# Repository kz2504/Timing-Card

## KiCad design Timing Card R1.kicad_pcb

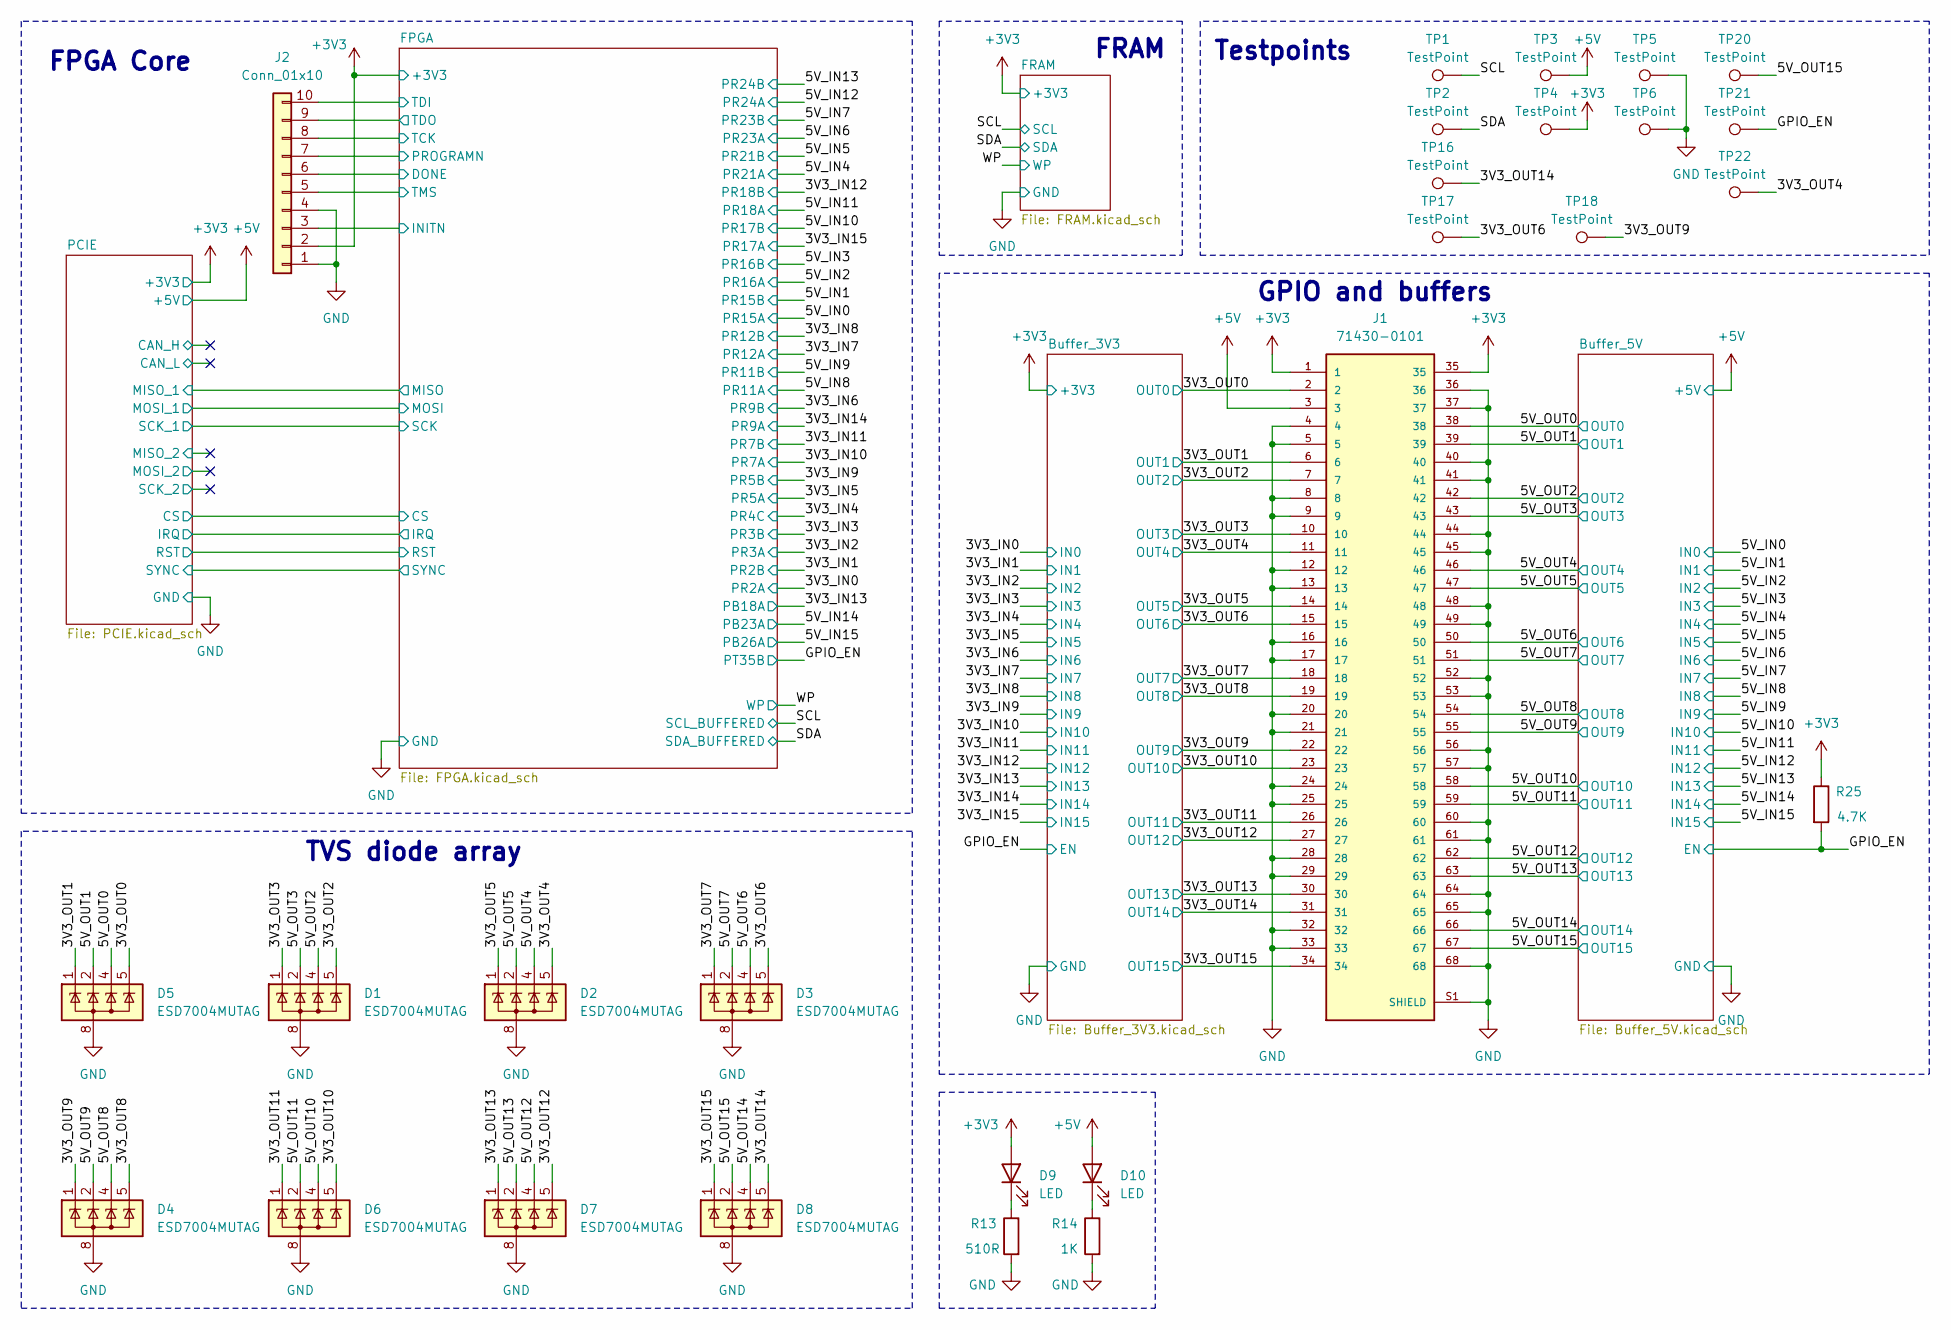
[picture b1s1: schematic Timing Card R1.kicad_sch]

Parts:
D1, D2, D3, D4, D5, D6, D7, D8: ESD7004MUTAG; Diodes_UDFN-10_1x2.5mm_P0.5mm_Modified
D9, D10: LED; LED_0805_2012Metric
J1: 71430-0101; MOLEX_71430-0101; PARTREV N
J2: Conn_01x10; PinHeader_2x05_P2.54mm_Vertical
R13: 510R; R_0805_2012Metric
R14: 1K; R_0805_2012Metric
R25: 4.7K; R_0805_2012Metric
TP1, TP2, TP3, TP4, TP5, TP6, TP16, TP17, TP18, TP20, TP21, TP22: TestPoint; TestPoint_Pad_D1.0mm

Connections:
+3V3: D9.2 (A), J1.1, J1.35, J2.2, R25.1, TP4.1; also elsewhere on the board
+5V: D10.2 (A), J1.3, TP3.1; also elsewhere on the board
/3V3_OUT0: D5.5 (K), J1.2; also elsewhere on the board
/3V3_OUT1: D5.1 (K), J1.6; also elsewhere on the board
/3V3_OUT2: D1.5 (K), J1.7; also elsewhere on the board
/3V3_OUT3: D1.1 (K), J1.10; also elsewhere on the board
/3V3_OUT4: D2.5 (K), J1.11, TP22.1; also elsewhere on the board
/3V3_OUT5: D2.1 (K), J1.14; also elsewhere on the board
/3V3_OUT6: D3.5 (K), J1.15, TP17.1; also elsewhere on the board
/3V3_OUT7: D3.1 (K), J1.18; also elsewhere on the board
/3V3_OUT8: D4.5 (K), J1.19; also elsewhere on the board
/3V3_OUT9: D4.1 (K), J1.22, TP18.1; also elsewhere on the board
/3V3_OUT10: D6.5 (K), J1.23; also elsewhere on the board
/3V3_OUT11: D6.1 (K), J1.26; also elsewhere on the board
/3V3_OUT12: D7.5 (K), J1.27; also elsewhere on the board
/3V3_OUT13: D7.1 (K), J1.30; also elsewhere on the board
/3V3_OUT14: D8.5 (K), J1.31, TP16.1; also elsewhere on the board
/3V3_OUT15: D8.1 (K), J1.34; also elsewhere on the board
/5V_OUT0: D5.4 (K), J1.38; also elsewhere on the board
/5V_OUT1: D5.2 (K), J1.39; also elsewhere on the board
/5V_OUT2: D1.4 (K), J1.42; also elsewhere on the board
/5V_OUT3: D1.2 (K), J1.43; also elsewhere on the board
/5V_OUT4: D2.4 (K), J1.46; also elsewhere on the board
/5V_OUT5: D2.2 (K), J1.47; also elsewhere on the board
/5V_OUT6: D3.4 (K), J1.50; also elsewhere on the board
/5V_OUT7: D3.2 (K), J1.51; also elsewhere on the board
/5V_OUT8: D4.4 (K), J1.54; also elsewhere on the board
/5V_OUT9: D4.2 (K), J1.55; also elsewhere on the board
/5V_OUT10: D6.4 (K), J1.58; also elsewhere on the board
/5V_OUT11: D6.2 (K), J1.59; also elsewhere on the board
/5V_OUT12: D7.4 (K), J1.62; also elsewhere on the board
/5V_OUT13: D7.2 (K), J1.63; also elsewhere on the board
/5V_OUT14: D8.4 (K), J1.66; also elsewhere on the board
/5V_OUT15: D8.2 (K), J1.67, TP20.1; also elsewhere on the board
/FPGA/DONE: J2.6; also elsewhere on the board
/FPGA/INITN: J2.3; also elsewhere on the board
/FPGA/PROGRAMN: J2.7; also elsewhere on the board
/FPGA/TCK: J2.8; also elsewhere on the board
/FPGA/TDI: J2.10; also elsewhere on the board
/FPGA/TDO: J2.9; also elsewhere on the board
/FPGA/TMS: J2.5; also elsewhere on the board
/GPIO_EN: R25.2, TP21.1; also elsewhere on the board
/SCL: TP1.1; also elsewhere on the board
/SDA: TP2.1; also elsewhere on the board
GND: D1.3 (A), D1.8 (A), D2.3 (A), D2.8 (A), D3.3 (A), D3.8 (A), D4.3 (A), D4.8 (A), D5.3 (A), D5.8 (A), D6.3 (A), D6.8 (A), D7.3 (A), D7.8 (A), D8.3 (A), D8.8 (A), J1.4, J1.5, J1.8, J1.9, J1.12, J1.13, J1.16, J1.17, J1.20, J1.21, J1.24, J1.25, J1.28, J1.29, J1.32, J1.33, J1.36, J1.37, J1.40, J1.41, J1.44, J1.45, J1.48, J1.49, J1.52, J1.53, J1.56, J1.57, J1.60, J1.61, J1.64, J1.65, J1.68, J1.S1 (SHIELD), J1.S2 (SHIELD), J2.1, J2.4, R13.2, R14.2, TP5.1, TP6.1; also elsewhere on the board
unnamed: D9.1 (K), R13.1
unnamed: D10.1 (K), R14.1

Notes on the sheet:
FRAM
FPGA Core
Testpoints
GPIO and buffers
TVS diode array

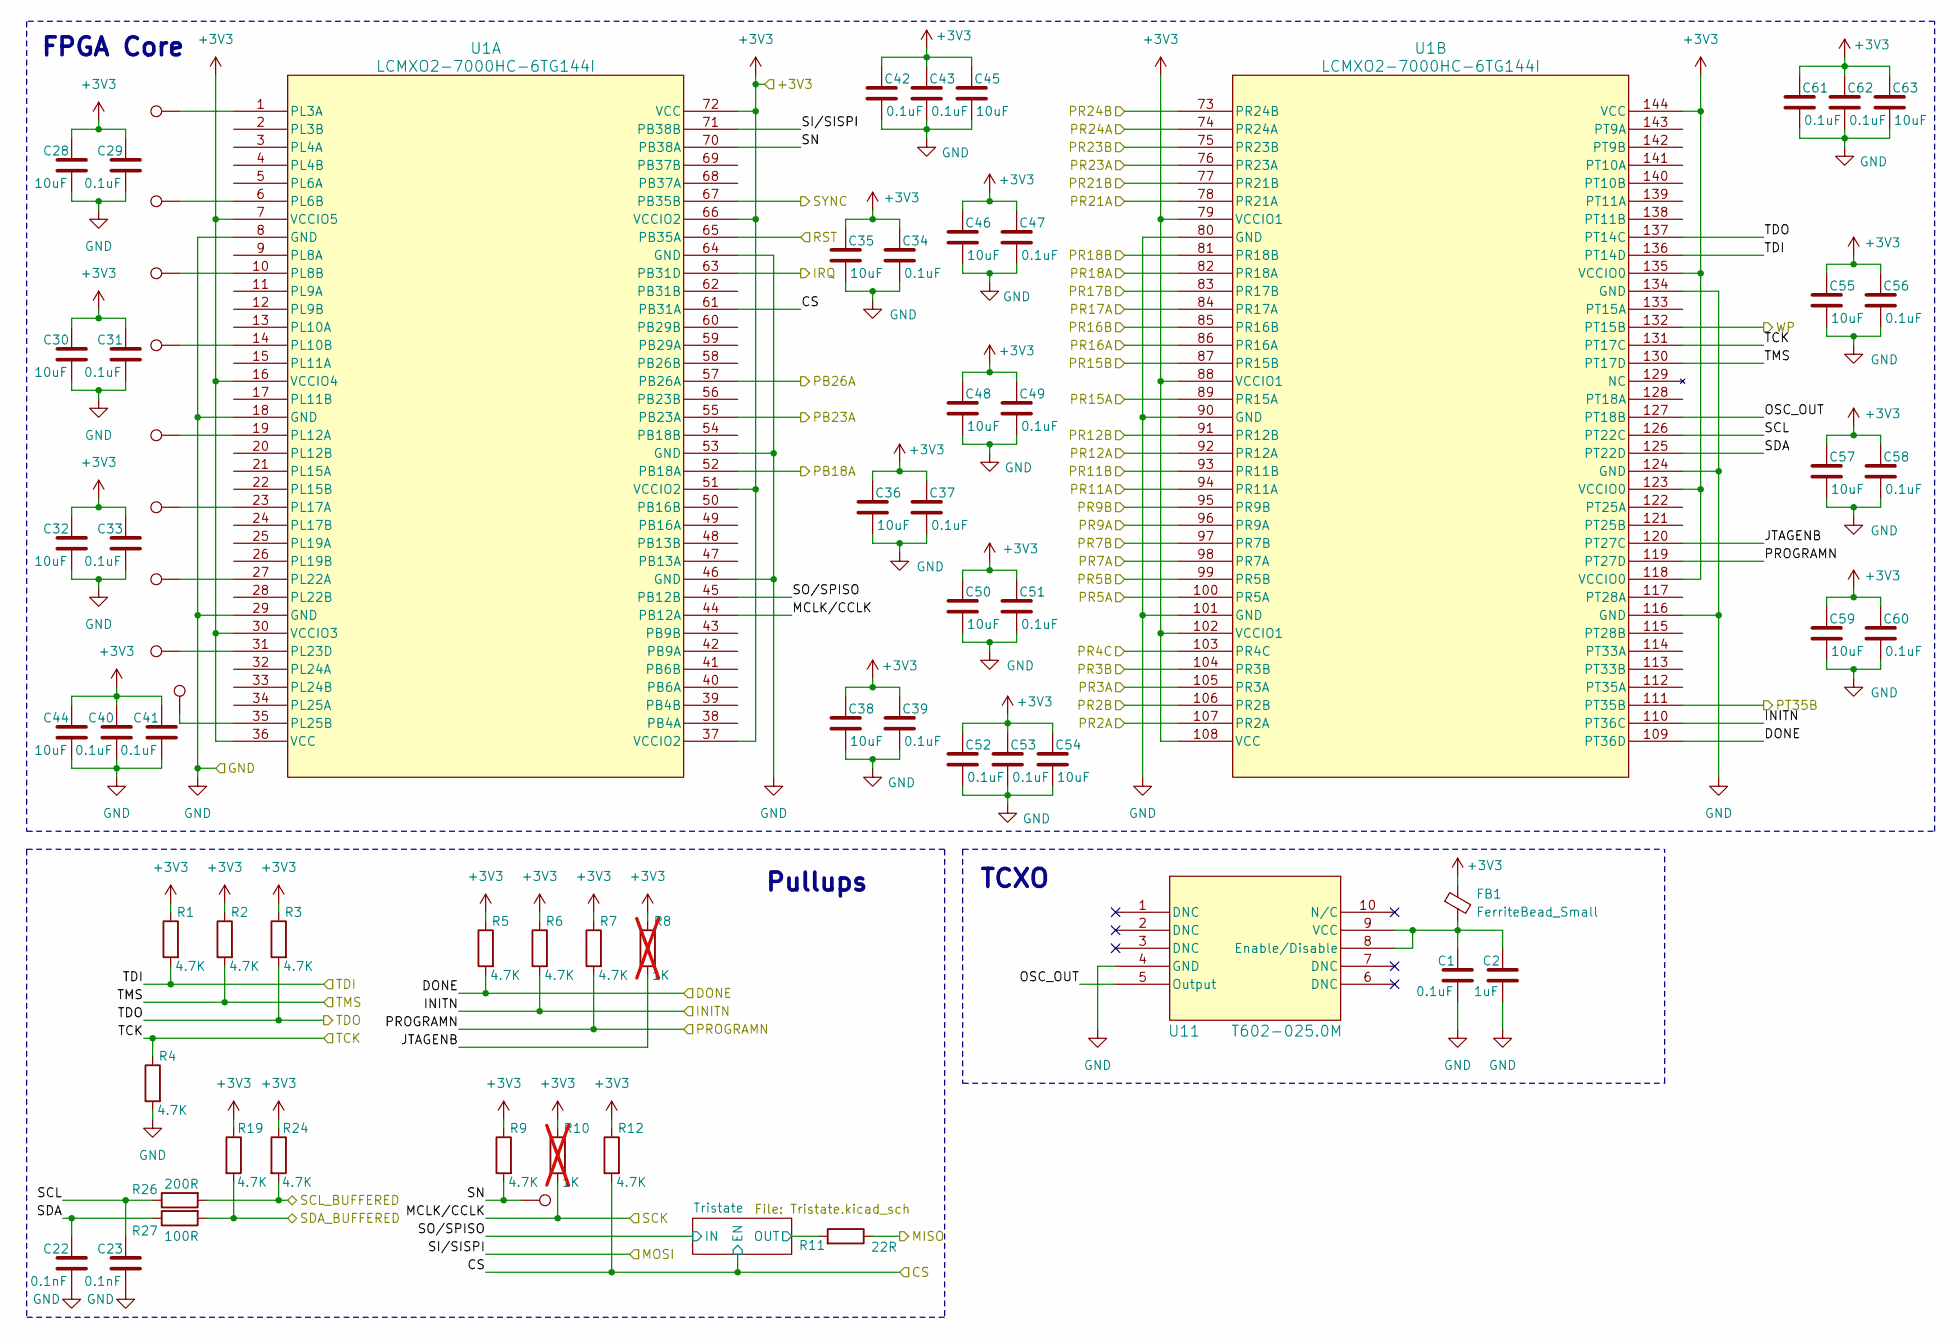
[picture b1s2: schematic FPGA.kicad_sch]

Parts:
C1: 0.1uF; C_0805_2012Metric
C2: 1uF; C_0805_2012Metric
C22, C23: 0.1nF; C_0805_2012Metric
C28, C30, C32, C35, C36, C38, C44, C45, C46, C48, C50, C54, C55, C57, C59, C63: 10uF; C_0603_1608Metric
C29, C31, C33, C34, C37, C39, C40, C41, C42, C43, C47, C49, C51, C52, C53, C56, C58, C60, C61, C62: 0.1uF; C_0603_1608Metric
FB1: FerriteBead_Small; L_0805_2012Metric
R1, R2, R3, R4, R5, R6, R7, R9, R12, R19, R24: 4.7K; R_0805_2012Metric
R8, R10: 1K; R_0805_2012Metric; not fitted
R11: 22R; R_0805_2012Metric
R26: 200R; R_0805_2012Metric
R27: 100R; R_0805_2012Metric
TP7, TP8, TP9, TP10, TP11, TP12, TP13, TP14, TP15: TestPoint; TestPoint_Pad_1.0x1.0mm
TP19: TestPoint; TestPoint_Pad_D1.0mm
U1: LCMXO2-7000HC-6TG144I; TQFP144_LAT
U11: T602-025.0M; T602-025.0M_CNW

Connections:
+3V3: C28.1, C29.1, C30.1, C31.1, C32.1, C33.1, C34.1, C35.1, C36.1, C37.1, C38.1, C39.1, C40.1, C41.1, C42.1, C43.1, C44.1, C45.1, C46.1, C47.1, C48.1, C49.1, C50.1, C51.1, C52.1, C53.1, C54.1, C55.1, C56.1, C57.1, C58.1, C59.1, C60.1, C61.1, C62.1, C63.1, FB1.1, R1.1, R2.1, R3.1, R5.1, R6.1, R7.1, R8.1, R9.1, R10.1, R12.1, R19.1, R24.1, U1.7 (VCCIO5), U1.16 (VCCIO4), U1.30 (VCCIO3), U1.36 (VCC), U1.37 (VCCIO2), U1.51 (VCCIO2), U1.66 (VCCIO2), U1.72 (VCC), U1.79 (VCCIO1), U1.88 (VCCIO1), U1.102 (VCCIO1), U1.108 (VCC), U1.118 (VCCIO0), U1.123 (VCCIO0), U1.135 (VCCIO0), U1.144 (VCC); also elsewhere on the board
/3V3_IN0: U1.107 (PR2A); also elsewhere on the board
/3V3_IN1: U1.106 (PR2B); also elsewhere on the board
/3V3_IN2: U1.105 (PR3A); also elsewhere on the board
/3V3_IN3: U1.104 (PR3B); also elsewhere on the board
/3V3_IN4: U1.103 (PR4C); also elsewhere on the board
/3V3_IN5: U1.100 (PR5A); also elsewhere on the board
/3V3_IN6: U1.95 (PR9B); also elsewhere on the board
/3V3_IN7: U1.92 (PR12A); also elsewhere on the board
/3V3_IN8: U1.91 (PR12B); also elsewhere on the board
/3V3_IN9: U1.99 (PR5B); also elsewhere on the board
/3V3_IN10: U1.98 (PR7A); also elsewhere on the board
/3V3_IN11: U1.97 (PR7B); also elsewhere on the board
/3V3_IN12: U1.81 (PR18B); also elsewhere on the board
/3V3_IN13: U1.52 (PB18A); also elsewhere on the board
/3V3_IN14: U1.96 (PR9A); also elsewhere on the board
/3V3_IN15: U1.84 (PR17A); also elsewhere on the board
/5V_IN0: U1.89 (PR15A); also elsewhere on the board
/5V_IN1: U1.87 (PR15B); also elsewhere on the board
/5V_IN2: U1.86 (PR16A); also elsewhere on the board
/5V_IN3: U1.85 (PR16B); also elsewhere on the board
/5V_IN4: U1.78 (PR21A); also elsewhere on the board
/5V_IN5: U1.77 (PR21B); also elsewhere on the board
/5V_IN6: U1.76 (PR23A); also elsewhere on the board
/5V_IN7: U1.75 (PR23B); also elsewhere on the board
/5V_IN8: U1.94 (PR11A); also elsewhere on the board
/5V_IN9: U1.93 (PR11B); also elsewhere on the board
/5V_IN10: U1.83 (PR17B); also elsewhere on the board
/5V_IN11: U1.82 (PR18A); also elsewhere on the board
/5V_IN12: U1.74 (PR24A); also elsewhere on the board
/5V_IN13: U1.73 (PR24B); also elsewhere on the board
/5V_IN14: U1.55 (PB23A); also elsewhere on the board
/5V_IN15: U1.57 (PB26A); also elsewhere on the board
/FPGA/CS: R12.2, U1.61 (PB31A); also elsewhere on the board
/FPGA/DONE: R5.2, U1.109 (PT36D); also elsewhere on the board
/FPGA/INITN: R6.2, U1.110 (PT36C); also elsewhere on the board
/FPGA/IRQ: U1.63 (PB31D); also elsewhere on the board
/FPGA/JTAGENB: R8.2, U1.120 (PT27C)
/FPGA/MCLK/CCLK: R10.2, U1.44 (PB12A); also elsewhere on the board
/FPGA/MISO: R11.1; also elsewhere on the board
/FPGA/OSC_OUT: U1.127 (PT18B), U11.5 (Output)
/FPGA/PROGRAMN: R7.2, U1.119 (PT27D); also elsewhere on the board
/FPGA/RST: U1.65 (PB35A); also elsewhere on the board
/FPGA/SCL: C23.1, R26.1, U1.126 (PT22C)
/FPGA/SDA: C22.1, R27.1, U1.125 (PT22D)
/FPGA/SI/SISPI: U1.71 (PB38B); also elsewhere on the board
/FPGA/SN: R9.2, TP19.1, U1.70 (PB38A)
/FPGA/SO/SPISO: U1.45 (PB12B); also elsewhere on the board
/FPGA/SYNC: U1.67 (PB35B); also elsewhere on the board
/FPGA/TCK: R4.1, U1.131 (PT17C); also elsewhere on the board
/FPGA/TDI: R1.2, U1.136 (PT14D); also elsewhere on the board
/FPGA/TDO: R3.2, U1.137 (PT14C); also elsewhere on the board
/FPGA/TMS: R2.2, U1.130 (PT17D); also elsewhere on the board
/FPGA/Tristate/OUT: R11.2; also elsewhere on the board
/GPIO_EN: U1.111 (PT35B); also elsewhere on the board
/SCL: R24.2, R26.2; also elsewhere on the board
/SDA: R19.2, R27.2; also elsewhere on the board
/WP: U1.132 (PT15B); also elsewhere on the board
GND: C1.2, C2.2, C22.2, C23.2, C28.2, C29.2, C30.2, C31.2, C32.2, C33.2, C34.2, C35.2, C36.2, C37.2, C38.2, C39.2, C40.2, C41.2, C42.2, C43.2, C44.2, C45.2, C46.2, C47.2, C48.2, C49.2, C50.2, C51.2, C52.2, C53.2, C54.2, C55.2, C56.2, C57.2, C58.2, C59.2, C60.2, C61.2, C62.2, C63.2, R4.2, U1.8 (GND), U1.18 (GND), U1.29 (GND), U1.46 (GND), U1.53 (GND), U1.64 (GND), U1.80 (GND), U1.90 (GND), U1.101 (GND), U1.116 (GND), U1.124 (GND), U1.134 (GND), U11.4 (GND); also elsewhere on the board
unnamed: TP7.1, U1.1 (PL3A)
unnamed: TP8.1, U1.6 (PL6B)
unnamed: TP9.1, U1.10 (PL8B)
unnamed: TP10.1, U1.14 (PL10B)
unnamed: TP11.1, U1.19 (PL12A)
unnamed: TP12.1, U1.23 (PL17A)
unnamed: TP13.1, U1.27 (PL22A)
unnamed: TP14.1, U1.31 (PL23D)
unnamed: TP15.1, U1.35 (PL25B)
unnamed: C1.1, C2.1, FB1.2, U11.8 (Enable/Disable), U11.9 (VCC)

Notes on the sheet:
TCXO
Pullups
FPGA Core

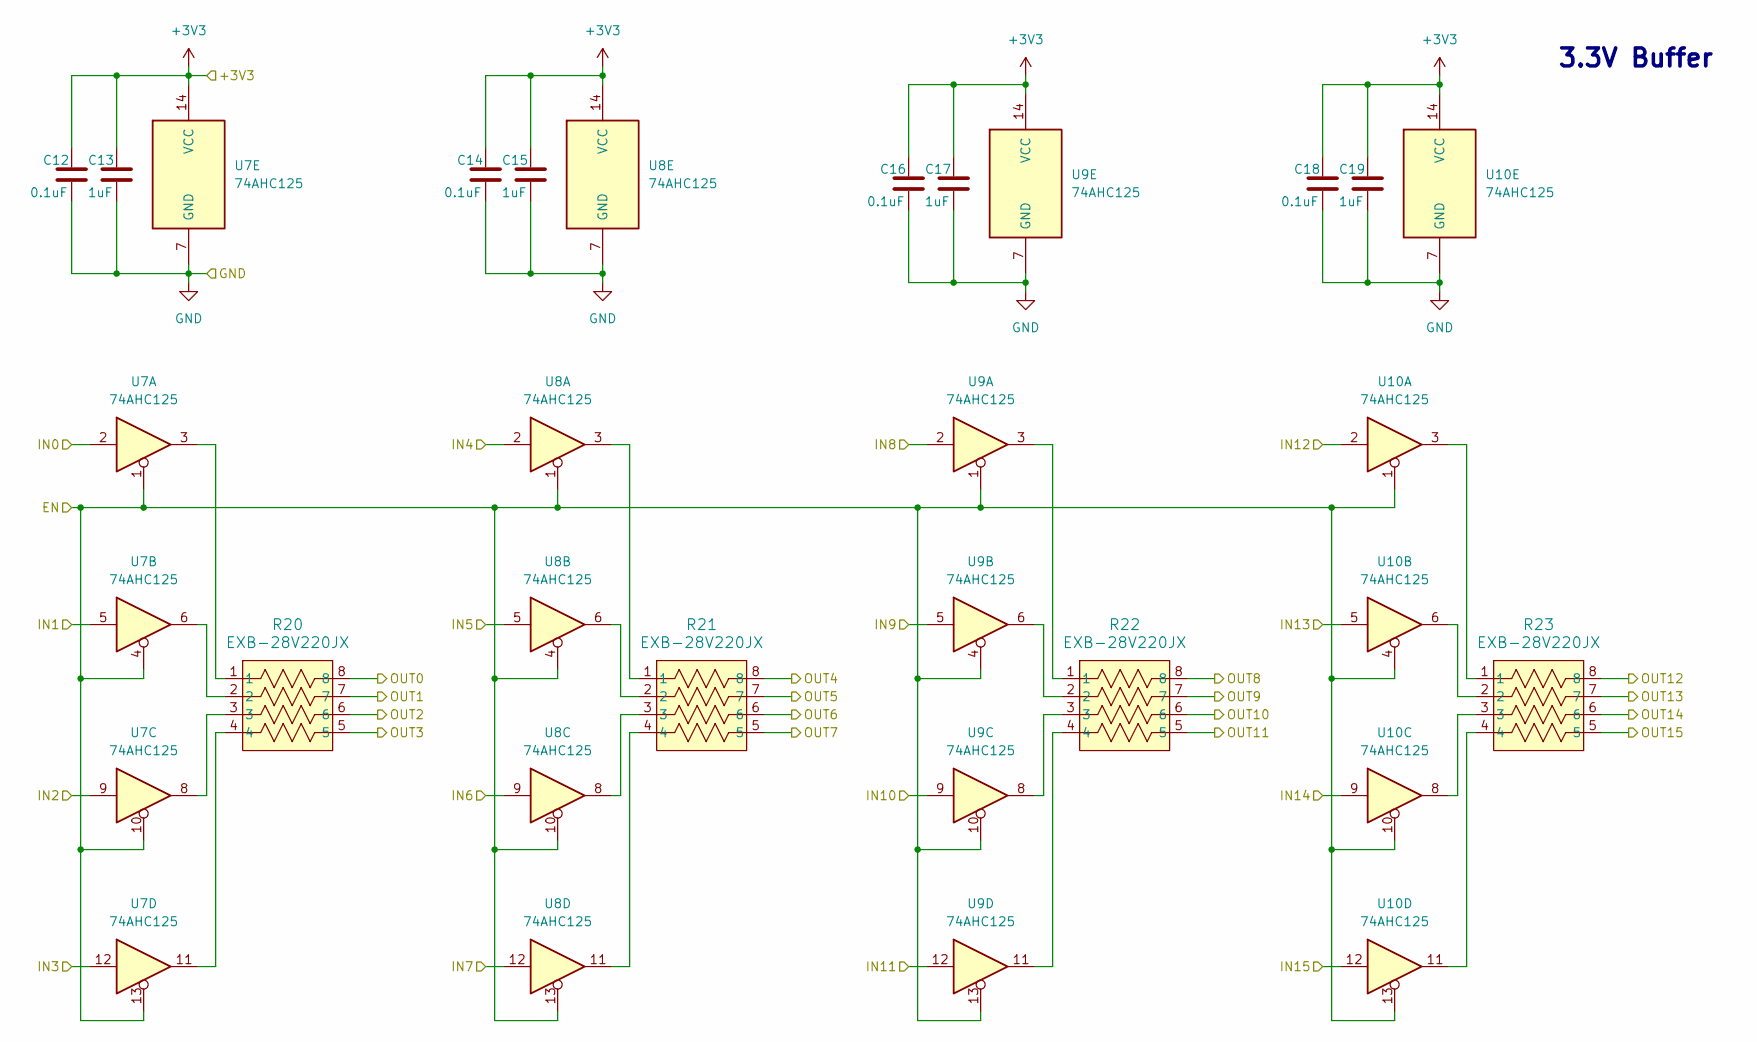
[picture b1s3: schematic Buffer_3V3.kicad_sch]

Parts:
C12, C14, C16, C18: 0.1uF; C_0805_2012Metric
C13, C15, C17, C19: 1uF; C_0805_2012Metric
R20, R21, R22, R23: EXB-28V220JX; EXB28V_PAN
U7, U8, U9, U10: 74AHC125; TSSOP-14_4.4x5mm_P0.65mm

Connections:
+3V3: C12.1, C13.1, C14.1, C15.1, C16.1, C17.1, C18.1, C19.1, U7.14 (VCC), U8.14 (VCC), U9.14 (VCC), U10.14 (VCC); also elsewhere on the board
/3V3_IN0: U7.2; also elsewhere on the board
/3V3_IN1: U7.5; also elsewhere on the board
/3V3_IN2: U7.9; also elsewhere on the board
/3V3_IN3: U7.12; also elsewhere on the board
/3V3_IN4: U8.2; also elsewhere on the board
/3V3_IN5: U8.5; also elsewhere on the board
/3V3_IN6: U8.9; also elsewhere on the board
/3V3_IN7: U8.12; also elsewhere on the board
/3V3_IN8: U9.2; also elsewhere on the board
/3V3_IN9: U9.5; also elsewhere on the board
/3V3_IN10: U9.9; also elsewhere on the board
/3V3_IN11: U9.12; also elsewhere on the board
/3V3_IN12: U10.2; also elsewhere on the board
/3V3_IN13: U10.5; also elsewhere on the board
/3V3_IN14: U10.9; also elsewhere on the board
/3V3_IN15: U10.12; also elsewhere on the board
/3V3_OUT0: R20.8; also elsewhere on the board
/3V3_OUT1: R20.7; also elsewhere on the board
/3V3_OUT2: R20.6; also elsewhere on the board
/3V3_OUT3: R20.5; also elsewhere on the board
/3V3_OUT4: R21.8; also elsewhere on the board
/3V3_OUT5: R21.7; also elsewhere on the board
/3V3_OUT6: R21.6; also elsewhere on the board
/3V3_OUT7: R21.5; also elsewhere on the board
/3V3_OUT8: R22.8; also elsewhere on the board
/3V3_OUT9: R22.7; also elsewhere on the board
/3V3_OUT10: R22.6; also elsewhere on the board
/3V3_OUT11: R22.5; also elsewhere on the board
/3V3_OUT12: R23.8; also elsewhere on the board
/3V3_OUT13: R23.7; also elsewhere on the board
/3V3_OUT14: R23.6; also elsewhere on the board
/3V3_OUT15: R23.5; also elsewhere on the board
/GPIO_EN: U7.1, U7.4, U7.10, U7.13, U8.1, U8.4, U8.10, U8.13, U9.1, U9.4, U9.10, U9.13, U10.1, U10.4, U10.10, U10.13; also elsewhere on the board
GND: C12.2, C13.2, C14.2, C15.2, C16.2, C17.2, C18.2, C19.2, U7.7 (GND), U8.7 (GND), U9.7 (GND), U10.7 (GND); also elsewhere on the board
unnamed: R20.1, U7.3
unnamed: R20.2, U7.6
unnamed: R20.3, U7.8
unnamed: R20.4, U7.11
unnamed: R21.1, U8.3
unnamed: R21.2, U8.6
unnamed: R21.3, U8.8
unnamed: R21.4, U8.11
unnamed: R22.1, U9.3
unnamed: R22.2, U9.6
unnamed: R22.3, U9.8
unnamed: R22.4, U9.11
unnamed: R23.1, U10.3
unnamed: R23.2, U10.6
unnamed: R23.3, U10.8
unnamed: R23.4, U10.11

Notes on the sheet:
3.3V Buffer

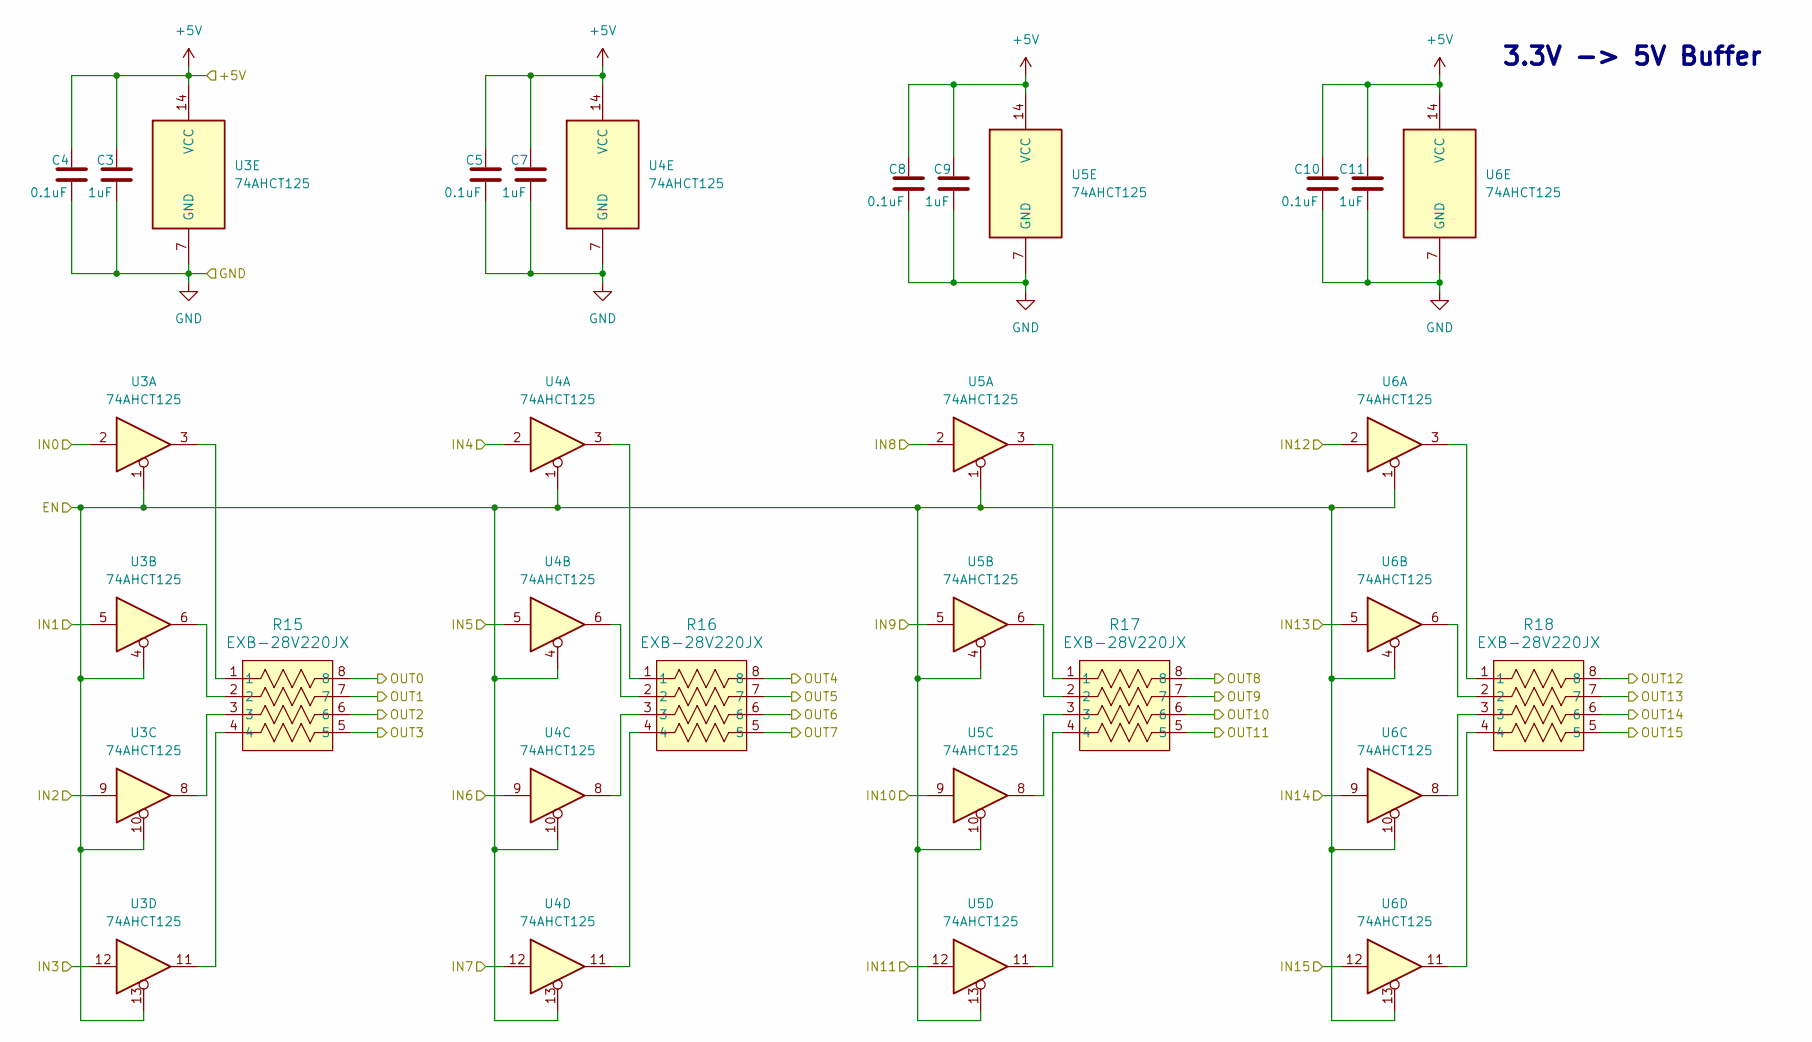
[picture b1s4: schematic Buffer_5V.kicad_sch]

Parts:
C3, C7, C9, C11: 1uF; C_0805_2012Metric
C4, C5, C8, C10: 0.1uF; C_0805_2012Metric
R15, R16, R17, R18: EXB-28V220JX; EXB28V_PAN
U3, U4, U5, U6: 74AHCT125; TSSOP-14_4.4x5mm_P0.65mm

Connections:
+5V: C3.1, C4.1, C5.1, C7.1, C8.1, C9.1, C10.1, C11.1, U3.14 (VCC), U4.14 (VCC), U5.14 (VCC), U6.14 (VCC); also elsewhere on the board
/5V_IN0: U3.2; also elsewhere on the board
/5V_IN1: U3.5; also elsewhere on the board
/5V_IN2: U3.9; also elsewhere on the board
/5V_IN3: U3.12; also elsewhere on the board
/5V_IN4: U4.2; also elsewhere on the board
/5V_IN5: U4.5; also elsewhere on the board
/5V_IN6: U4.9; also elsewhere on the board
/5V_IN7: U4.12; also elsewhere on the board
/5V_IN8: U5.2; also elsewhere on the board
/5V_IN9: U5.5; also elsewhere on the board
/5V_IN10: U5.9; also elsewhere on the board
/5V_IN11: U5.12; also elsewhere on the board
/5V_IN12: U6.2; also elsewhere on the board
/5V_IN13: U6.5; also elsewhere on the board
/5V_IN14: U6.9; also elsewhere on the board
/5V_IN15: U6.12; also elsewhere on the board
/5V_OUT0: R15.8; also elsewhere on the board
/5V_OUT1: R15.7; also elsewhere on the board
/5V_OUT2: R15.6; also elsewhere on the board
/5V_OUT3: R15.5; also elsewhere on the board
/5V_OUT4: R16.8; also elsewhere on the board
/5V_OUT5: R16.7; also elsewhere on the board
/5V_OUT6: R16.6; also elsewhere on the board
/5V_OUT7: R16.5; also elsewhere on the board
/5V_OUT8: R17.8; also elsewhere on the board
/5V_OUT9: R17.7; also elsewhere on the board
/5V_OUT10: R17.6; also elsewhere on the board
/5V_OUT11: R17.5; also elsewhere on the board
/5V_OUT12: R18.8; also elsewhere on the board
/5V_OUT13: R18.7; also elsewhere on the board
/5V_OUT14: R18.6; also elsewhere on the board
/5V_OUT15: R18.5; also elsewhere on the board
/GPIO_EN: U3.1, U3.4, U3.10, U3.13, U4.1, U4.4, U4.10, U4.13, U5.1, U5.4, U5.10, U5.13, U6.1, U6.4, U6.10, U6.13; also elsewhere on the board
GND: C3.2, C4.2, C5.2, C7.2, C8.2, C9.2, C10.2, C11.2, U3.7 (GND), U4.7 (GND), U5.7 (GND), U6.7 (GND); also elsewhere on the board
unnamed: R15.1, U3.3
unnamed: R15.2, U3.6
unnamed: R15.3, U3.8
unnamed: R15.4, U3.11
unnamed: R16.1, U4.3
unnamed: R16.2, U4.6
unnamed: R16.3, U4.8
unnamed: R16.4, U4.11
unnamed: R17.1, U5.3
unnamed: R17.2, U5.6
unnamed: R17.3, U5.8
unnamed: R17.4, U5.11
unnamed: R18.1, U6.3
unnamed: R18.2, U6.6
unnamed: R18.3, U6.8
unnamed: R18.4, U6.11

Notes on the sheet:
3.3V -> 5V Buffer

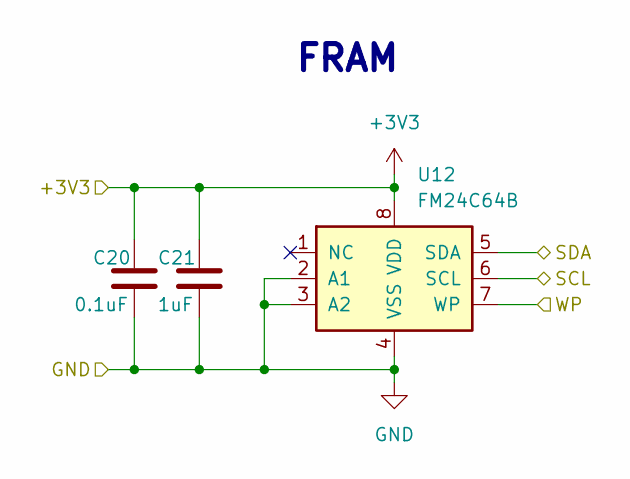
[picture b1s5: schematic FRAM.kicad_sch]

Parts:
C20: 0.1uF; C_0805_2012Metric
C21: 1uF; C_0805_2012Metric
U12: FM24C64B; SOIC-8_3.9x4.9mm_P1.27mm

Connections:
+3V3: C20.1, C21.1, U12.8 (VDD); also elsewhere on the board
/SCL: U12.6 (SCL); also elsewhere on the board
/SDA: U12.5 (SDA); also elsewhere on the board
/WP: U12.7 (WP); also elsewhere on the board
GND: C20.2, C21.2, U12.2 (A1), U12.3 (A2), U12.4 (VSS); also elsewhere on the board

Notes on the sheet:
FRAM

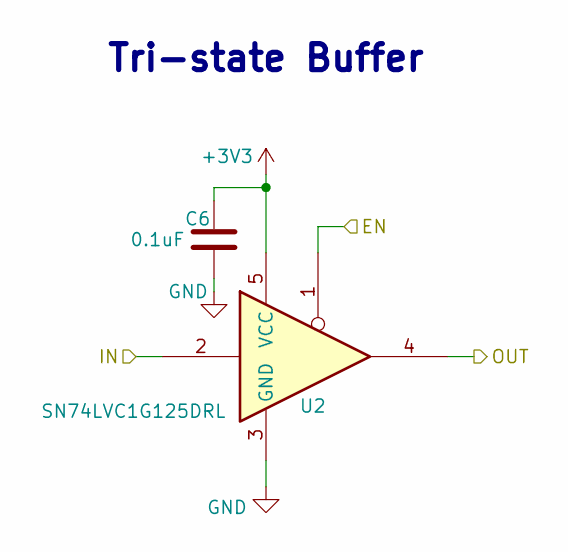
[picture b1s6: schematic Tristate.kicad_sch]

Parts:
C6: 0.1uF; C_0805_2012Metric
U2: SN74LVC1G125DRL; Texas_R-PDSO-N5_DRL-5

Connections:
+3V3: C6.1, U2.5 (VCC); also elsewhere on the board
/FPGA/CS: U2.1; also elsewhere on the board
/FPGA/SO/SPISO: U2.2; also elsewhere on the board
/FPGA/Tristate/OUT: U2.4; also elsewhere on the board
GND: C6.2, U2.3 (GND); also elsewhere on the board

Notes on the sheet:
Tri-state Buffer

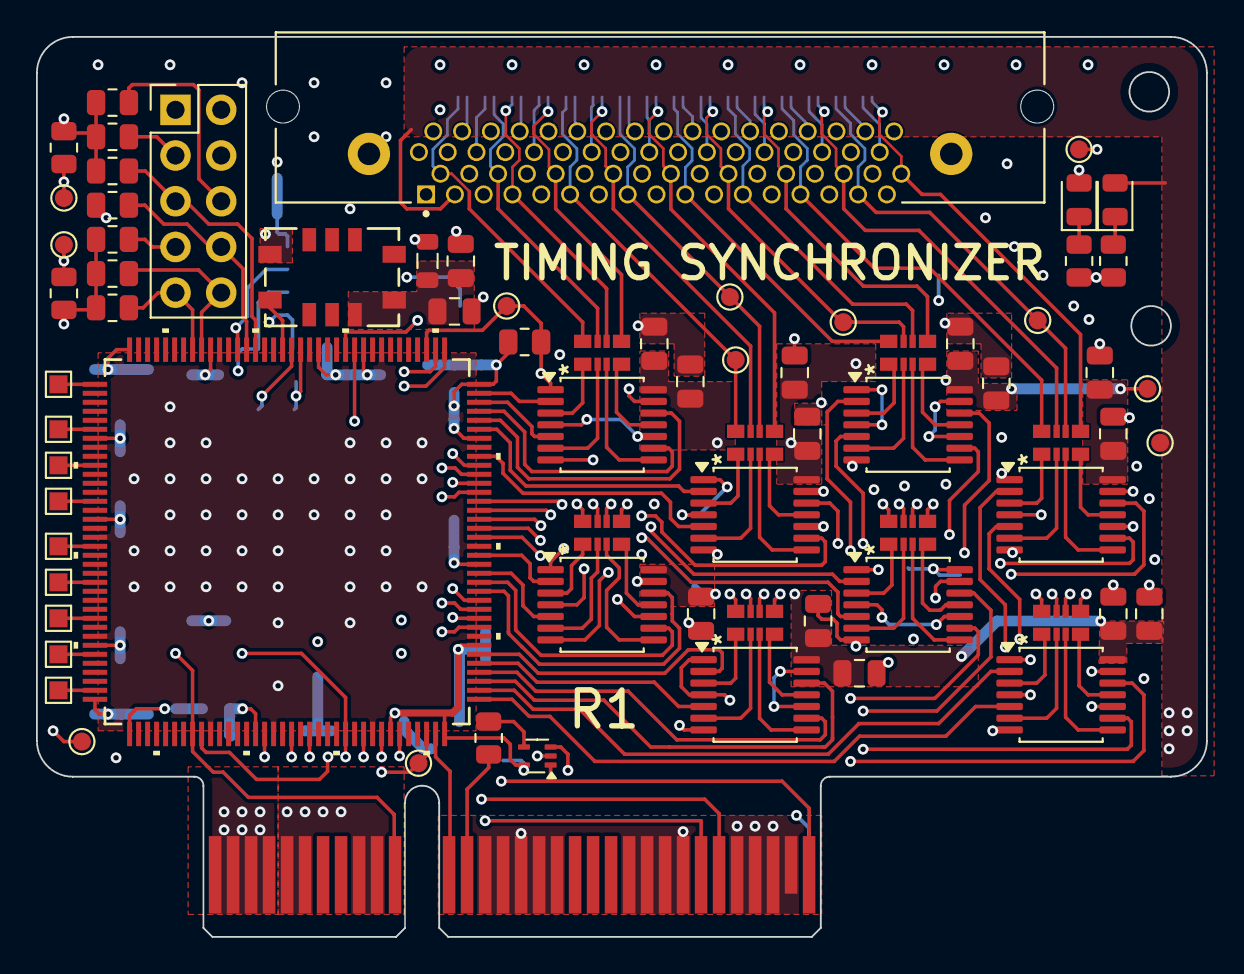
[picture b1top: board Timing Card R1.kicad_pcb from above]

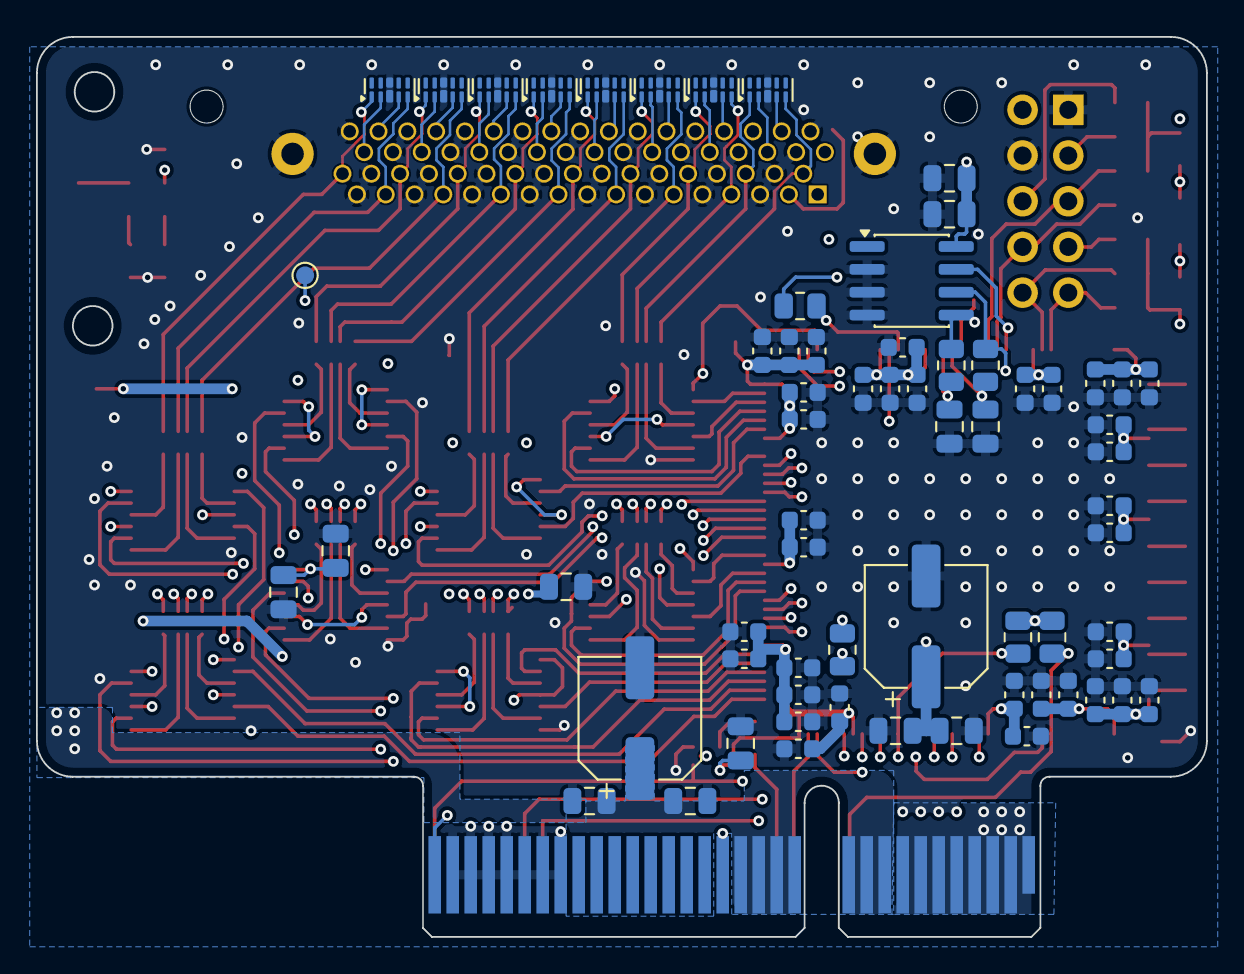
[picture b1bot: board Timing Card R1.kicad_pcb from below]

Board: 4 copper layers, 65.0 x 50.0 mm, 140 parts (66 on the bottom side), 136 nets.

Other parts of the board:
C88, C91: 0.1uF; C_0805_2012Metric
C89, C93: 1uF; C_0805_2012Metric
C90, C96: 10uF; CP_Elec_6.3x5.9
J10: 10018784-10201TLF; BUS_PCIexpress_x4

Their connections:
+3V3: C88.1, C89.1, C90.1, J10.A1, J10.A2, J10.A3, J10.A4, J10.A5, J10.A6, J10.A7, J10.A8, J10.B1, J10.B2, J10.B3, J10.B4; also elsewhere on the board
+5V: C91.1, C93.1, C96.1, J10.A9, J10.A10, J10.A11, J10.A12, J10.A13, J10.A14, J10.A15; also elsewhere on the board
/FPGA/CS: J10.B32; also elsewhere on the board
/FPGA/IRQ: J10.A32; also elsewhere on the board
/FPGA/MCLK/CCLK: J10.B11; also elsewhere on the board
/FPGA/MISO: J10.B13; also elsewhere on the board
/FPGA/RST: J10.B26; also elsewhere on the board
/FPGA/SI/SISPI: J10.B12; also elsewhere on the board
/FPGA/SYNC: J10.B27; also elsewhere on the board
GND: C88.2, C89.2, C90.2, C91.2, C93.2, C96.2, J10.A16, J10.A25, J10.A26, J10.A27, J10.A28, J10.A29, J10.A30, J10.A31, J10.B5, J10.B6, J10.B9, J10.B10, J10.B14, J10.B15, J10.B16, J10.B17, J10.B18, J10.B22, J10.B23, J10.B24, J10.B25, J10.B28, J10.B29, J10.B30, J10.B31; also elsewhere on the board

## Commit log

2026-02-18 Fixed board size
2026-02-20 Updates for R2
